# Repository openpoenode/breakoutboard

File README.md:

# Overview

The **Breakout Board** carrier is designed to let developers explore the full feature set of the openPoeNode module before committing to a custom carrier design. It includes a range of practical features to simplify testing, evaluation, and firmware debugging.

# Features

The Breakout Board provides a single slot for an openPoeNode module with any supported output voltage. An onboard DC/DC converter is included to step down 5V module output to 3.3V for MCU supply.

## Supply Voltage Selector

The MCU section can be powered from one of three sources:

- Module V<sub>out</sub> directly (for 3.3V modules)
- V<sub>buck</sub> – output of the onboard DC/DC converter (V<sub>out</sub> → 3.3V)
- V<sub>prog</sub> – supplied by an external programmer or debugger

Select the desired source by placing a jumper cap on the corresponding pins.

Although the module includes overvoltage protection, avoid supplying 5V directly to the MCU section.

When powering the board via an external programmer, ensure it can provide sufficient current. Insufficient current may cause unstable behavior during programming (e.g., flash writes failing due to brownouts). If this occurs, use an external power adapter and select V<sub>buck</sub> as the supply source.

## Programming Header

Connector for an external programmer or debugger. The pinout matches the ESP-Prog board from Espressif.

## GPIO Block

All module GPIOs are broken out to this header for general-purpose use. Pin numbering follows the ESP32-D0WD-V3 datasheet.

## Ethernet Control Block

Three GPIOs are required to control the Ethernet interface (**GPIO2 / GPIO13 / GPIO15**). These are routed next to the corresponding **MDC / MDIO / Enable** pins.

- For normal operation, place jumper caps across each row to bridge the signals.
- For testing alternative pin assignments, the signals can be rerouted to other GPIOs using jumper wires.

## LED and Switches

The Breakout Board includes two tactile switches and one RGBW LED for quick testing.

### Switches

- Integrated pull-ups and hardware debouncing
- Output is pulled low when pressed

### LED

- Each channel’s anode is connected to 3.3V via a current-limiting resistor
- Cathodes are exposed on the header and can be driven by open-collector GPIOs

## Configuration DIP Switches

A 6-position DIP switch enables convenient hardware configuration during development:

- **I²C pull-ups (GPIO32 / GPIO33)**
  - 2.2 kΩ pull-ups for easy interfacing with I²C devices
  - Enable with Switch 1 & 2

- **Power load resistors**
  - 100 Ω and 56 Ω resistors from V<sub>out</sub> to GND
  - Useful when very low power consumption causes PoE instability (minimum draw > 0.44 W)
  - Helps prevent PoE power cycling (“hiccup” behavior)
  - Enable individually with Switch 3 & 4

- **Power indicators**
  - LEDs for V<sub>out</sub> and 3.3V rails
  - Enable/disable with Switch 5 & 6 (useful for precise power measurements)

## External Power Adapter

If PoE is unavailable or needs to be overridden, the board can be powered using an external 36–54V DC source.

- Connector: 5.5 × 2.1 mm barrel jack
- Polarity: center positive

## Supply Voltage Block

Provides power outputs for external devices (e.g., sensors):

- V<sub>out</sub> (1x)
- 3.3V (2x)
- Digital GND (3x)

Ensure total consumption remains within the DC/DC converter limits:
- 5V module: up to 1.4A
- 3.3V module: up to 2.1A

## PoE Voltage Block

For advanced use cases, raw PoE input voltage is available for external DC/DC converters.

⚠️ This connector is not populated by default and should be used with caution.

## Supply Current Monitoring

An onboard current monitor IC helps track power consumption and stay within PoE and DC/DC converter limits (0.44W < P < 7W).

- Measures I<sub>out</sub> via a 22 mΩ shunt resistor
- Measure voltage at the test pad (relative to digital ground)
- Current (A) = measured voltage / 1.1

# Physical

- Dimensions: 74 × 55 mm
- PCB: 4-layer FR4, 1.60 mm thickness

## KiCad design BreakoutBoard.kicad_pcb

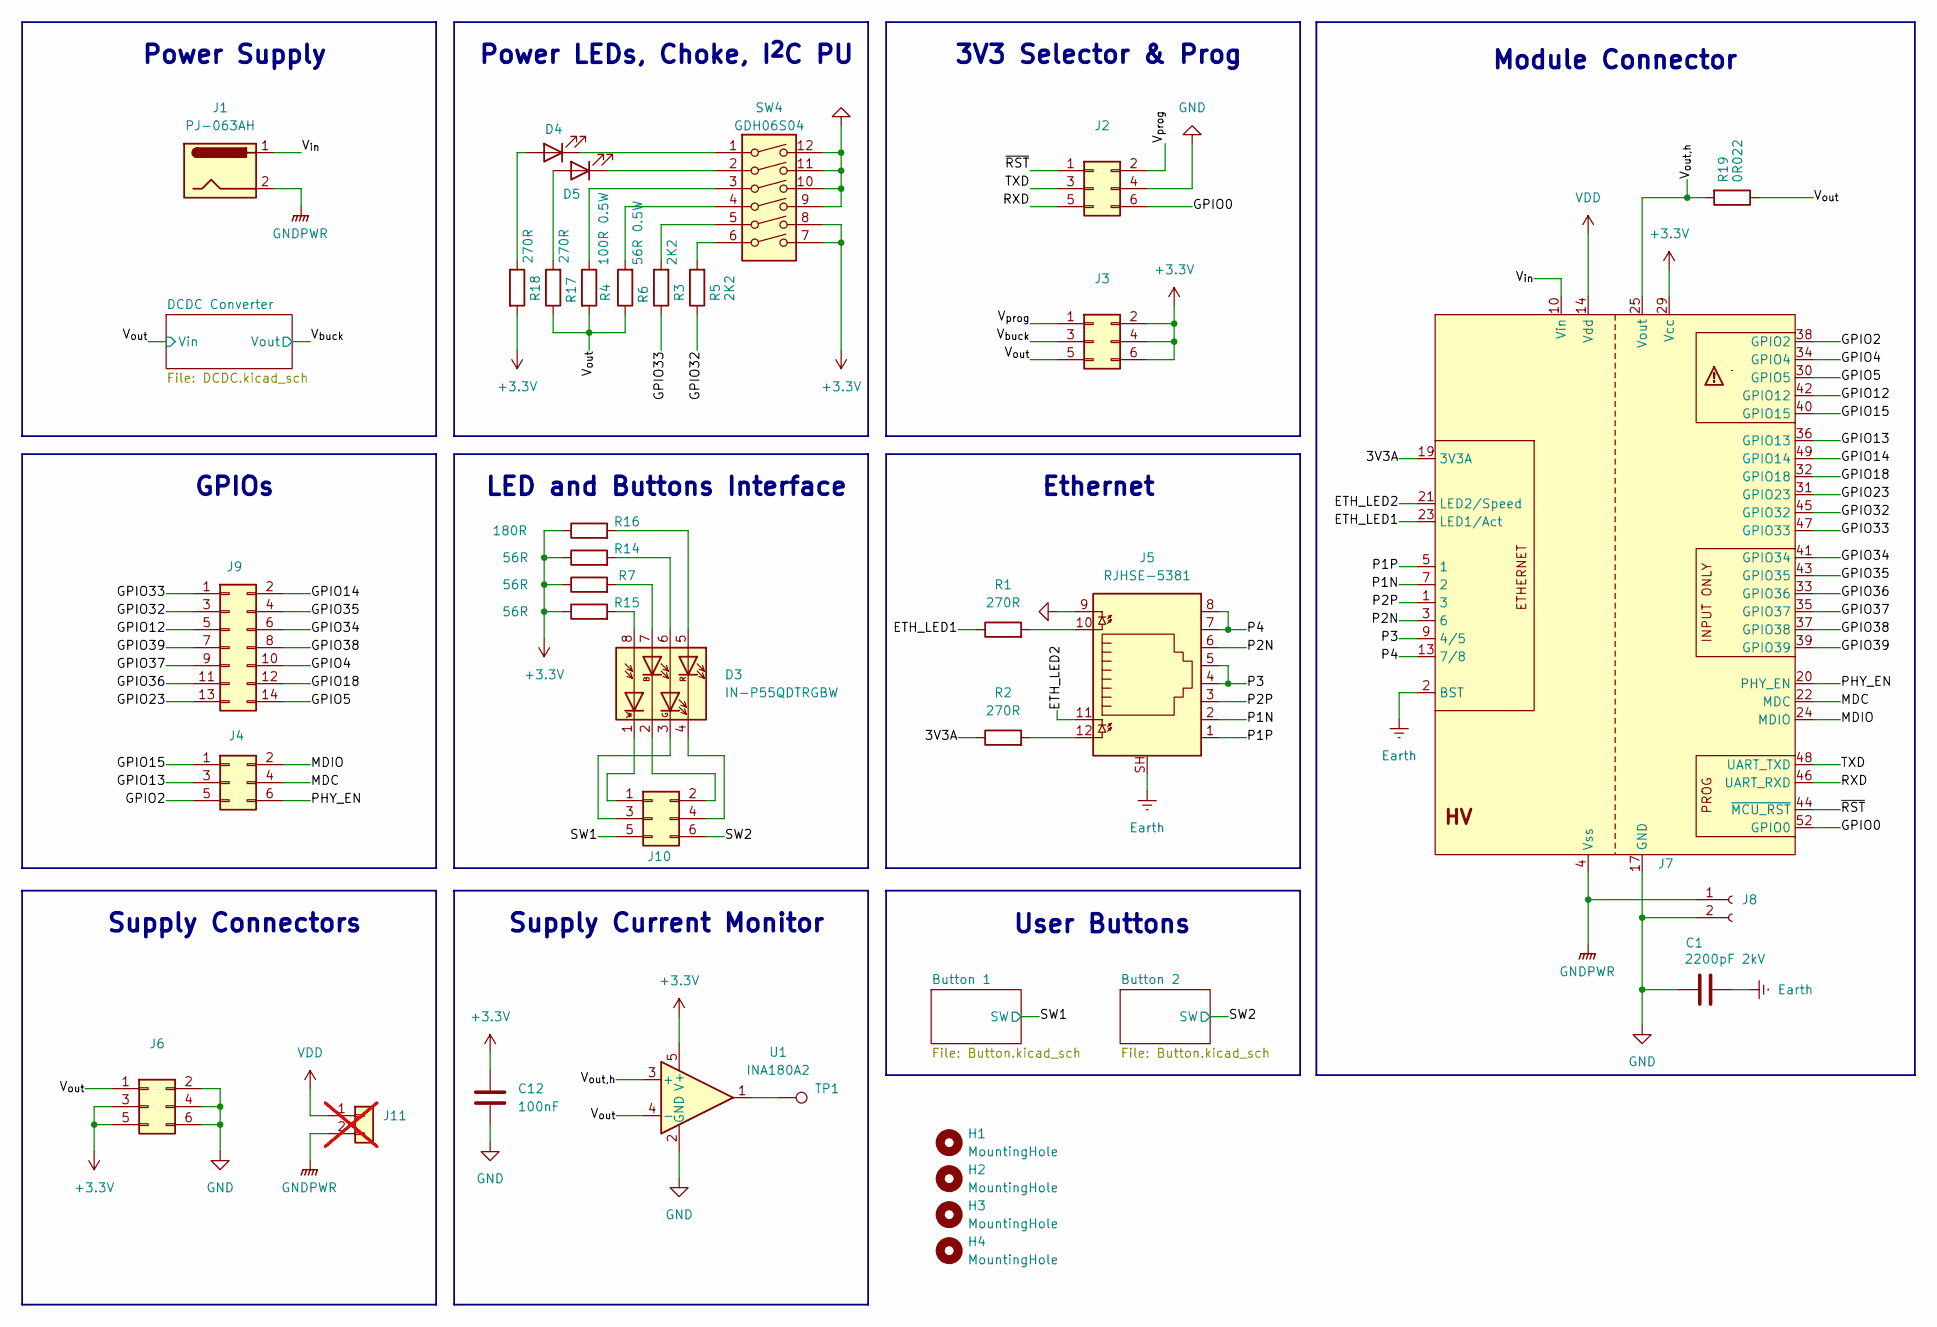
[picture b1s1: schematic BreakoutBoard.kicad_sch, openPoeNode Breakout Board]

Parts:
C1: 2200pF 2kV; C_1206_3216Metric; MOUSER# 581-1206GC222KAT2A
C12: 100nF; C_0805_2012Metric; MOUSER# 581-KGM21NR71H104KT
D3: IN-P55QDTRGBW; INP55QDTRGBW; MOUSER# 743-IN-P55QDTRGBW
D4, D5: Red; LED_0603_1608Metric; MOUSER# 720-KRELPS122VGVI23H
H1, H2, H3, H4: MountingHole; MountingHole_3.2mm_M3
J1: PJ-063AH; BarrelJack_CUI_PJ-063AH_Horizontal; MOUSER# 490-PJ-063AH
J2, J3, J4, J6, J10: 10129381-906001BLF; PinHeader_2x03_P2.54mm_Vertical; MOUSER# 649-1012938190601BLF
J5: RJHSE-5381; RJ45_Amphenol_RJHSE538X; MOUSER# 523-RJHSE-5381
J7: 119A-80A00-R02
J8: 119A-LATCH-80
J9: 10129381-914001BLF; PinHeader_2x07_P2.54mm_Vertical; MOUSER# 649-1012938191401BLF
J11: PinHeader_1x02_P2.54mm_Vertical; not fitted
R1, R2, R17, R18: 270R; R_0805_2012Metric; MOUSER# 791-WR08X2700FTL
R3, R5: 2K2; R_0805_2012Metric; MOUSER# 791-WR08X222JTL
R4: 100R 0.5W; R_0805_2012Metric; MOUSER# 71-CRCW0805100RFKEAH
R6: 56R 0.5W; R_0805_2012Metric; MOUSER# 660-SG73S2ATTD56R0F
R7, R14, R15: 56R; R_0805_2012Metric; MOUSER# 603-AC0805FR-0756RL
R16: 180R; R_0805_2012Metric; MOUSER# 603-RE0805FRE07180RL
R19: 0R022; R_0805_2012Metric; MOUSER# 667-ERJ-6CWFR022V
SW4: GDH06S04; MOUSER# 506-GDH06S04
TP1: TestPoint; TestPoint_Pad_D3.0mm
U1: INA180A2; SOT-23-5; MOUSER# 595-INA180A2IDBVT

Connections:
+3.3V: C12.2, J3.2, J3.4, J3.6, J6.3, J6.5, J7.29 (Vcc), R7.1, R14.1, R15.1, R16.1, R18.2, SW4.7, SW4.8, U1.5 (V+); also elsewhere on the board
/3V3A: J7.19 (3V3A), R2.1
/ETH_LED1: J7.23 (LED1/Act), R1.1
/ETH_LED2: J5.11, J7.21 (LED2/Speed)
/GPIO0: J2.6, J7.52 (GPIO0)
/GPIO2: J4.5, J7.38 (GPIO2)
/GPIO4: J7.34 (GPIO4), J9.10
/GPIO5: J7.30 (GPIO5), J9.14
/GPIO12: J7.42 (GPIO12), J9.5
/GPIO13: J4.3, J7.36 (GPIO13)
/GPIO14: J7.49 (GPIO14), J9.2
/GPIO15: J4.1, J7.40 (GPIO15)
/GPIO18: J7.32 (GPIO18), J9.12
/GPIO23: J7.31 (GPIO23), J9.13
/GPIO32: J7.45 (GPIO32), J9.3, R5.1
/GPIO33: J7.47 (GPIO33), J9.1, R3.1
/GPIO34: J7.41 (GPIO34), J9.6
/GPIO35: J7.43 (GPIO35), J9.4
/GPIO36: J7.33 (GPIO36), J9.11
/GPIO37: J7.35 (GPIO37), J9.9
/GPIO38: J7.37 (GPIO38), J9.8
/GPIO39: J7.39 (GPIO39), J9.7
/MDC: J4.4, J7.22 (MDC)
/MDIO: J4.2, J7.24 (MDIO)
/P1N: J5.2, J7.7 (2)
/P1P: J5.1, J7.5 (1)
/P2N: J5.6, J7.3 (6)
/P2P: J5.3, J7.1 (3)
/P3: J5.4, J5.5, J7.9 (4/5), J7.11 (4/5)
/P4: J5.7, J5.8, J7.13 (7/8), J7.15 (7/8)
/PHY_EN: J4.6, J7.20 (PHY_EN)
/RXD: J2.5, J7.46 (UART_RXD)
/SW1: J10.5; also elsewhere on the board
/SW2: J10.6; also elsewhere on the board
/TXD: J2.3, J7.48 (UART_TXD)
/V_{buck}: J3.3; also elsewhere on the board
/V_{out,h}: J7.25 (Vout), J7.26 (Vout), J7.27 (Vout), J7.28 (Vout), R19.2, U1.3 (+)
/V_{out}: J3.5, J6.1, R4.2, R6.1, R17.1, R19.1, U1.4 (-); also elsewhere on the board
/V_{prog}: J2.2, J3.1
/~RST: J2.1, J7.44 (~MCU_RST)
Earth: C1.2, J5.SH, J7.2 (BST)
GND: C1.1, C12.1, J2.4, J5.9, J6.2, J6.4, J6.6, J7.17 (GND), J7.18 (GND), J7.50 (GND), J7.51 (GND), J8.2, SW4.9, SW4.10, SW4.11, SW4.12, U1.2 (GND); also elsewhere on the board
GNDPWR: J1.2, J7.4 (Vss), J7.6 (Vss), J7.8 (Vss), J8.1, J11.2
unnamed: D3.7 (AB), R7.2
unnamed: D3.6 (AG), R14.2
unnamed: D3.5 (AR), R16.2
unnamed: D3.8 (AW), R15.2
unnamed: D3.2 (KB), J10.2
unnamed: D3.3 (KG), J10.3
unnamed: D3.4 (KR), J10.4
unnamed: D3.1 (KW), J10.1
unnamed: D4.2 (A), R18.1
unnamed: D4.1 (K), SW4.1
unnamed: D5.2 (A), R17.2
unnamed: D5.1 (K), SW4.2
unnamed: J5.10, R1.2
unnamed: J5.12, R2.2
unnamed: R3.2, SW4.5
unnamed: R4.1, SW4.3
unnamed: R5.2, SW4.6
unnamed: R6.2, SW4.4
unnamed: TP1.1, U1.1
VDD: J7.14 (Vdd), J7.16 (Vdd), J11.1
Vin: J1.1, J7.10 (Vin), J7.12 (Vin)

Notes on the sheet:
GPIOs
Supply Connectors
Module Connector
Power Supply
User Buttons
Supply Current Monitor
Power LEDs, Choke, I^{2}C PU
Ethernet
3V3 Selector & Prog
LED and Buttons Interface

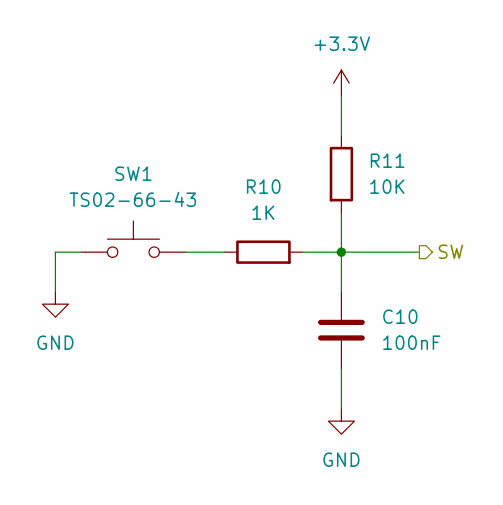
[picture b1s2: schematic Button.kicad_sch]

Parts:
C10: 100nF; C_0805_2012Metric; MOUSER# 581-KGM21NR71H104KT
R10: 1K; R_0805_2012Metric; MOUSER# 603-RC0805FR-101KL
R11: 10K; R_0805_2012Metric; MOUSER# 603-RC0805FR-7W10KL
SW1: TS02-66-43; SW_PUSH_6mm_H4.3mm; MOUSER# 179-TS026643BK100LCR

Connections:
+3.3V: R11.1; also elsewhere on the board
/SW1: C10.1, R10.2, R11.2; also elsewhere on the board
GND: C10.2, SW1.1; also elsewhere on the board
unnamed: R10.1, SW1.2

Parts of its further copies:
C11: 100nF; C_0805_2012Metric; MOUSER# 581-KGM21NR71H104KT
R12: 1K; R_0805_2012Metric; MOUSER# 603-RC0805FR-101KL
R13: 10K; R_0805_2012Metric; MOUSER# 603-RC0805FR-7W10KL
SW2: TS02-66-43; SW_PUSH_6mm_H4.3mm; MOUSER# 179-TS026643BK100LCR

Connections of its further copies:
+3.3V: R13.1; also elsewhere on the board
/SW2: C11.1, R12.2, R13.2; also elsewhere on the board
GND: C11.2, SW2.1; also elsewhere on the board
unnamed: R12.1, SW2.2

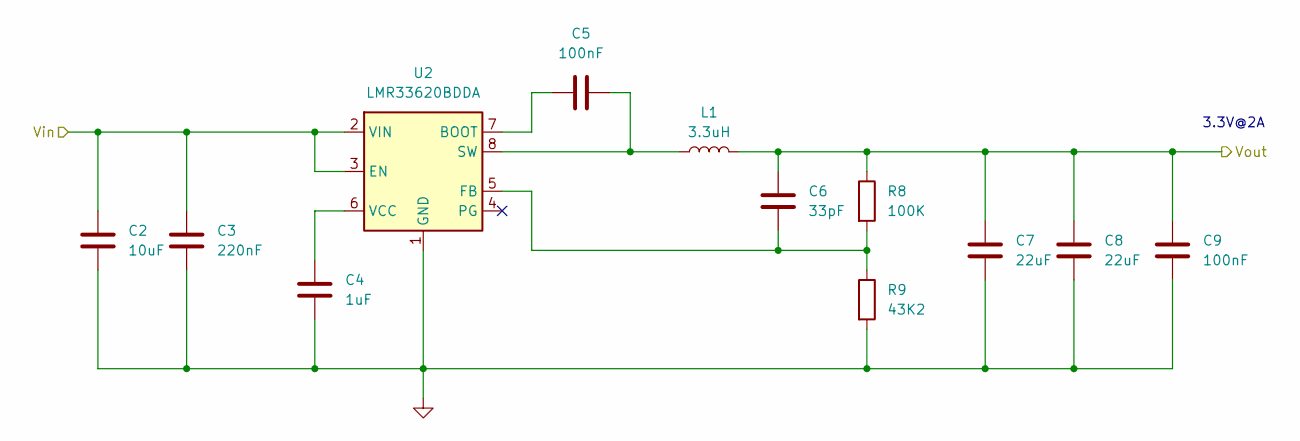
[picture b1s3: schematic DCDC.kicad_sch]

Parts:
C2: 10uF; C_1210_3225Metric; MOUSER# 810-C3225X7R1H106250
C3: 220nF; C_0805_2012Metric; MOUSER# 810-C2012X7R1H224K
C4: 1uF; C_0805_2012Metric; MOUSER# 187-CL21B105KAFNNNE
C5, C9: 100nF; C_0805_2012Metric; MOUSER# 581-KGM21NR71H104KT
C6: 33pF; C_0805_2012Metric; MOUSER# 80-C0805C330J5GACLR
C7, C8: 22uF; C_1210_3225Metric; MOUSER# 187-CL32B226KOJNNNE
L1: 3.3uH; L_Wuerth_MAPI-4030; MOUSER# 710-74438357033
R8: 100K; R_0805_2012Metric; MOUSER# 603-RE0805FRE07100KL
R9: 43K2; R_0805_2012Metric; MOUSER# 603-RC0805FR-0743K2L
U2: LMR33620BDDA; Texas_HSOP-8-1EP_3.9x4.9mm_P1.27mm_ThermalVias; MOUSER# 595-LMR33620BDDAR

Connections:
/V_{buck}: C6.1, C7.1, C8.1, C9.1, L1.2, R8.1; also elsewhere on the board
/V_{out}: C2.1, C3.1, U2.2 (VIN), U2.3 (EN); also elsewhere on the board
GND: C2.2, C3.2, C4.2, C7.2, C8.2, C9.2, R9.2, U2.1 (GND), U2.9 (GND); also elsewhere on the board
unnamed: C5.1, U2.7 (BOOT)
unnamed: C6.2, R8.2, R9.1, U2.5 (FB)
unnamed: C5.2, L1.1, U2.8 (SW)
unnamed: C4.1, U2.6 (VCC)

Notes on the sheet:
3.3V@2A

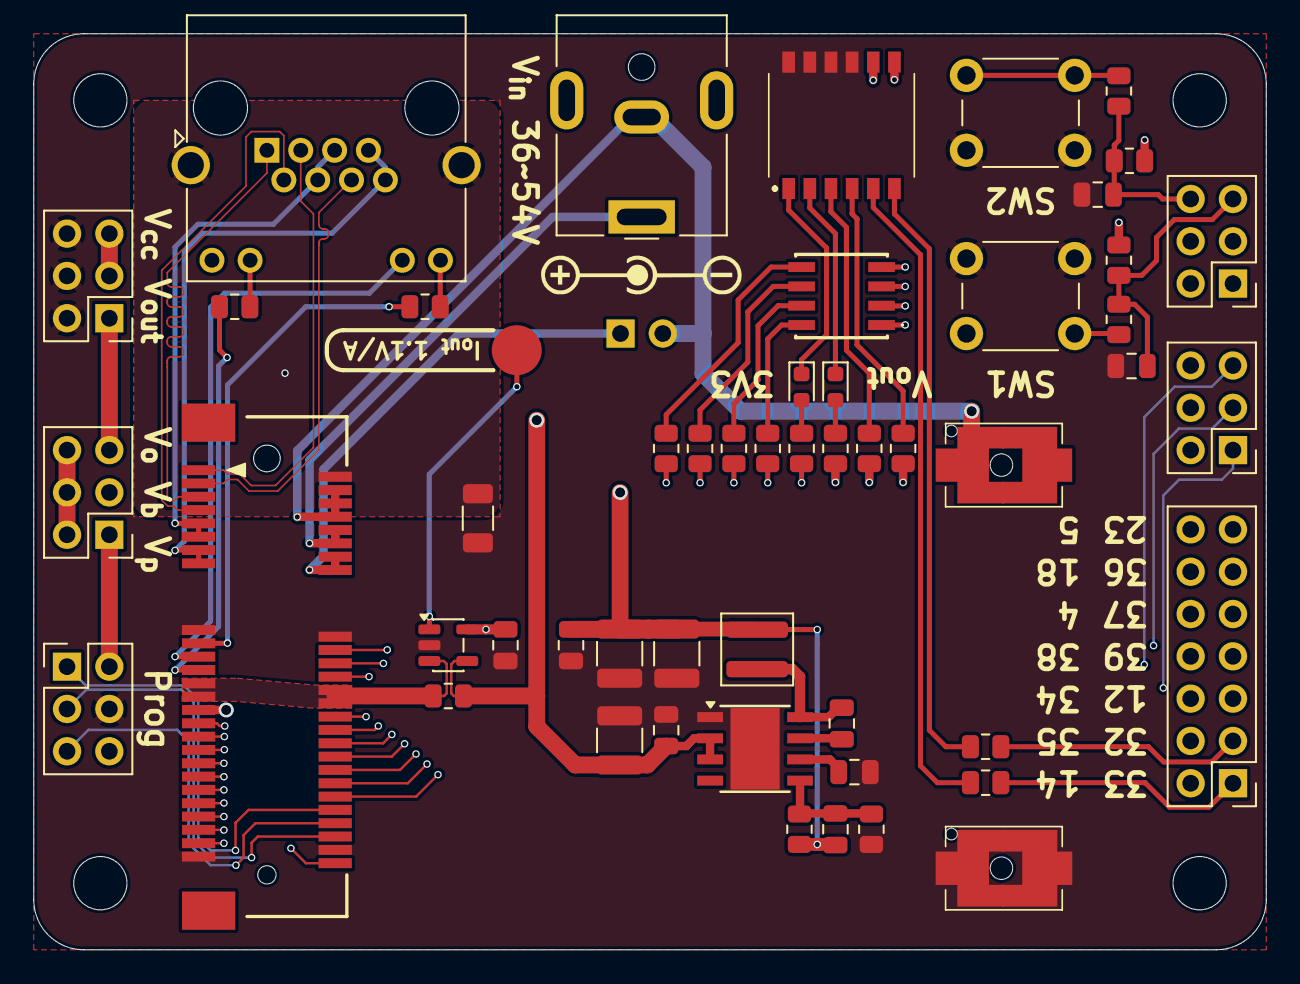
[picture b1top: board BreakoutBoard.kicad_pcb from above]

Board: 4 copper layers, 74.0 x 55.0 mm, 56 parts (0 on the bottom side), 70 nets.

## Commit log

2026-01-06 Create LICENSE
2026-01-22 updated DC jack 3D model moved reference designators on PCB added LED datasheet
2026-01-23 fixed wrong part number for tactile switches (leg length short -> long)
2026-02-15 updated RJ45 connector part number and fixed silk screen mistakes on GPIO numbering
2026-02-16 fixed RJ45 connector type value
2026-02-17 added revision silkscreen text
2026-02-19 completed routing for revision 0.2
2026-02-20 completed silk screen
2026-03-19 minor changes
2026-03-19 added IDAnything
2026-04-09 arranged reference designators
2026-04-13 added external adapter voltage and polarity clarification on silk screen
2026-04-20 added README.md
2026-04-22 removed comment

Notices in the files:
Button.kicad_sch:
LICENSED under CERN-OHL-S-2.0
